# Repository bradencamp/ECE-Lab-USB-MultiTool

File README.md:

# USB-ECE-Lab-Multitool
In recent years students have been required to purchase USB Laboratory Instruments such as the Analog Discovery 2 (AD2) from Digilent Inc or the Advanced Active Learning Module (ADALM 2000) from Analog Devices. These devices allow the students to complete Laboratory exercises at home and to experiment on their own time without the need to rely on open lab hours. The COVID pandemic created a high demand for such devices, as throughout the U.S. lab classes have been converted to at-home labs. This high demand in concert with the chip crises has propelled the price for these devices to currently $199 and $249 (academic price for the AD2 and AD3, respectively) and $237 (ADALM2000).

This USB Multi-function Laboratory Instrument will be inexpensive and therefore less capable than the AD2 or ADALM 2000 while still fulfilling the requirements for most laboratory exercises in the undergraduate ECE curriculum. This new device should use a microcontroller with analog front ends for the Oscilloscope and Wave Form Generator functionality. It should function as a 2-channel Oscilloscope and Arbitrary Waveform Generator (AWG) with a Bandwidth of up to 2 MHz and a sample rate of 5 Msps, a 16-channel logic analyzer, and be controllable via USB from a PC (Windows, Mac, and Linux) as well as offering live waveform viewing on a PC. The total part cost should not exceed $50. A similar project was once offered by the Opencope MZ (https://digilent.com/reference/test-and-measurement/openscope-mz/start) which has been discontinued.

Previous senior design projects have built a one-channel prototype for the oscilloscope and a two channel AWG. However, the oscilloscope did not fully meet the requirements. The arbitrary waveform generator function is complete. The logic analyzer is now a separate project and currently being designed. The goal of this project is to learn from the oscilloscope prototype and create one that meets the requirements and integrate the arbitrary waveform generator and the logic analyzer, all with an intuitive and easy to use graphical user interface on the PC using PyQtGraph. This project requires analog circuit design of amplifiers, filters, etc., while being cost-conscious. The fewer different parts are needed and the fewer parts are needed overall, the more likely you'll meet the $50 target. It also requires programming of an STM-32 microcontroller in C, GUI design and programming in Python.

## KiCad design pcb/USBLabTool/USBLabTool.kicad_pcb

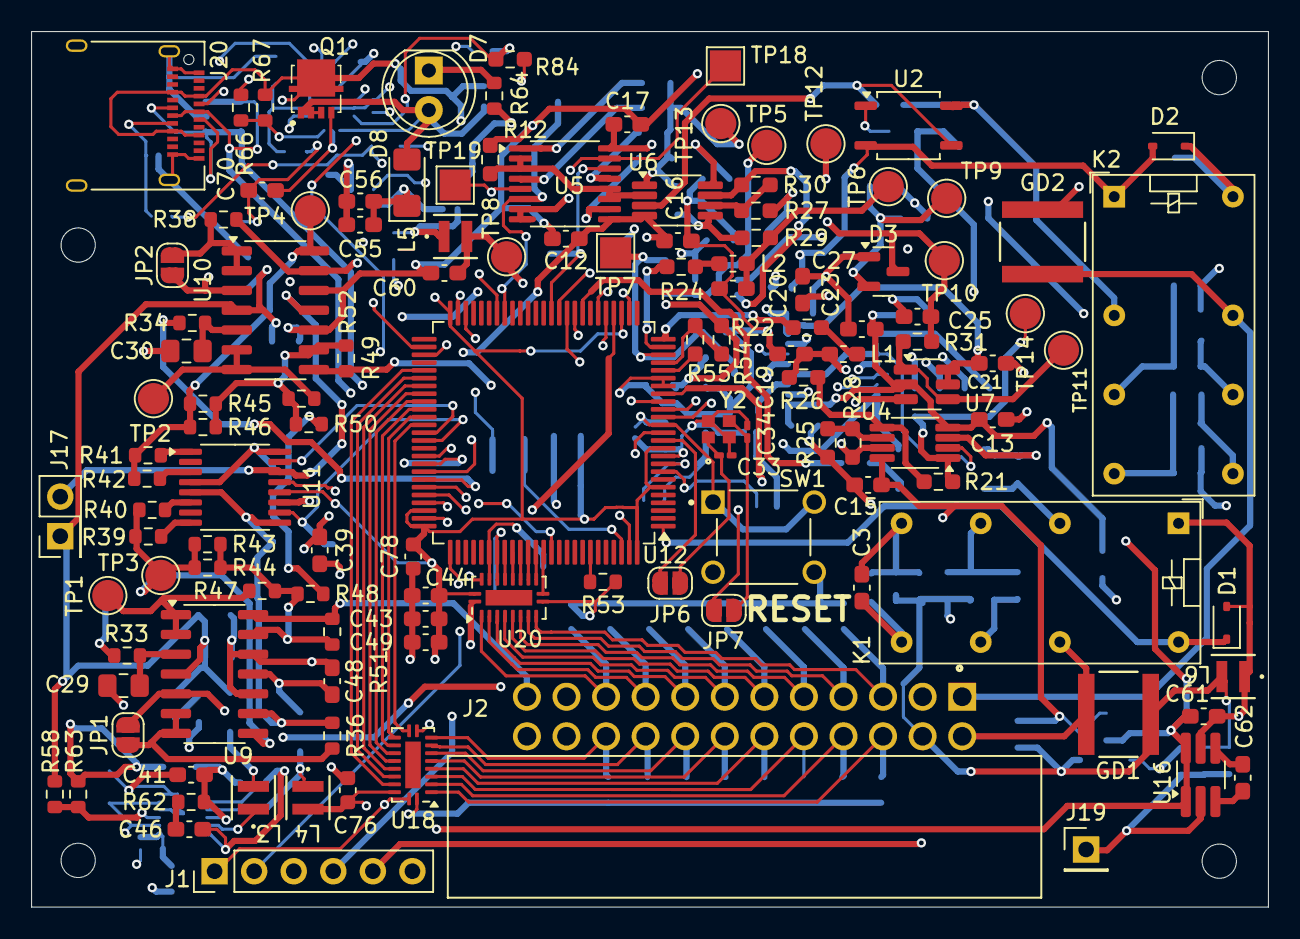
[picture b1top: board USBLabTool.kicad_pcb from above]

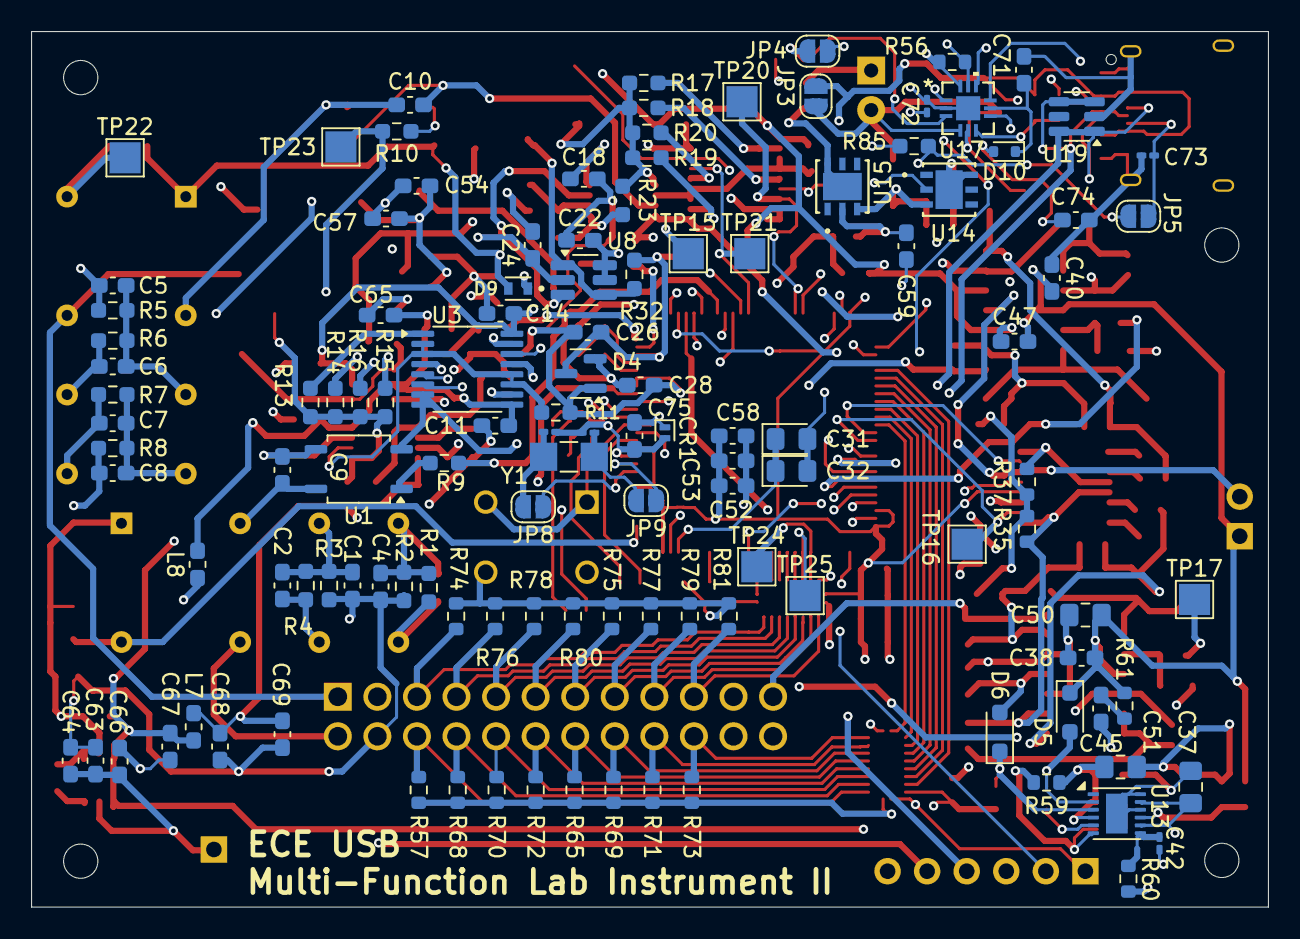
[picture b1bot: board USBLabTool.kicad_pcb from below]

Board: 4 copper layers, 79.4 x 56.2 mm, 250 parts (121 on the bottom side), 165 nets.

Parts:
C1, C5: 200p; C_0603_1608Metric_Pad1.08x0.95mm_HandSolder
C2, C4, C6, C8: 820p; C_0603_1608Metric_Pad1.08x0.95mm_HandSolder
C3, C7: 68p; C_0603_1608Metric_Pad1.08x0.95mm_HandSolder
C9, C10: 47n; C_0603_1608Metric_Pad1.08x0.95mm_HandSolder
C11, C12, C13, C14, C15, C16, C17, C18, C21, C22, C23, C24, C27, C28, C38, C39, C40, C41, C43, C44, C47, C48, C49, C52, C53, C54, C63, C64, C65, C67, C68, C69, C71, C75: 100n; C_0603_1608Metric_Pad1.08x0.95mm_HandSolder
C19, C20, C62: 1u; C_0603_1608Metric_Pad1.08x0.95mm_HandSolder
C25, C26: 160p; C_0603_1608Metric_Pad1.08x0.95mm_HandSolder
C29, C30, C37, C50, C51: 10u; C_0805_2012Metric_Pad1.18x1.45mm_HandSolder
C31, C32: 2.2u; D_0805_2012Metric_Pad1.15x1.40mm_HandSolder
C33, C34: 5.6p; C_0201_0603Metric_Pad0.64x0.40mm_HandSolder
C35, C36: 3.3p; C_0201_0603Metric_Pad0.64x0.40mm_HandSolder
C42: 100n; C_0201_0603Metric_Pad0.64x0.40mm_HandSolder
C45, C46: 120p; C_0603_1608Metric_Pad1.08x0.95mm_HandSolder
C55, C56, C58: 4.7uF; C_0603_1608Metric_Pad1.08x0.95mm_HandSolder
C57, C61, C66: 10u; C_0603_1608Metric_Pad1.08x0.95mm_HandSolder
C59, C60: 100nF; C_0603_1608Metric_Pad1.08x0.95mm_HandSolder
C70: DNF; C_0603_1608Metric_Pad1.08x0.95mm_HandSolder
C72, C73: 330p; C_0201_0603Metric_Pad0.64x0.40mm_HandSolder
C74: 2.2u; C_0603_1608Metric_Pad1.08x0.95mm_HandSolder
C76, C78: 100nF; C_0603_1608Metric
CR1: ESDALC6V1-1M2; D_SOD-882
D1, D2: 1N4148WS; D_SOD-323
D3, D4: BAV99; SOT-23
D5, D6: NSR0530; D_SOD-323_HandSoldering
D7: LED; LED_D5.0mm
D8: D_Schottky; D_1206_3216Metric_Pad1.42x1.75mm_HandSolder
D9: ESDA25P35-1U1M; TVS_ESDA25P35-1U1M
D10: BAT54KFILM; D_SOD-523
GD1, GD2: GDT_SH90; GDT_SH_LTF
H1, H2, H3, H4: MountingHole; MountingHole_2.2mm_M2
J1: Conn_01x06_Pin; PinHeader_1x06_P2.54mm_Vertical
J2: Conn_02x12_Odd_Even; OST_302-R241
J17: 2x01; PinHeader_2x01_P2.54mm_Vertical
J19: T_N5V; PinHeader_1x01_P2.54mm_Vertical
J20: USB_C_Receptacle; USB_C_Receptacle_Amphenol_12401610E4-2A
JP1, JP2, JP3, JP4, JP5, JP6, JP7, JP8, JP9: SJ; SolderJumper-2_P1.3mm_Open_RoundedPad1.0x1.5mm
K1, K2: G5V-2; Relay_DPDT_Omron_G5V-2
L1, L2: 10uH; L_0603_1608Metric_Pad1.05x0.95mm_HandSolder
L3, L4, L5, L6: 4.7uH; IND_TAIYO_NRH2410_TAY
L7, L8: 4.7uH; L_0603_1608Metric_Pad1.05x0.95mm_HandSolder
Q1: STL11N3LLH6; STL20N6F7
R1, R3, R5, R7: 820K; R_0603_1608Metric_Pad0.98x0.95mm_HandSolder
R2, R8: 68K; R_0603_1608Metric_Pad0.98x0.95mm_HandSolder
R4, R6: 200k; R_0603_1608Metric_Pad0.98x0.95mm_HandSolder
R9, R10: 240; R_0603_1608Metric_Pad0.98x0.95mm_HandSolder
R11, R12, R21, R23, R28, R30: 1K; R_0603_1608Metric_Pad0.98x0.95mm_HandSolder
R13, R17, R22, R24: 6.2; R_0603_1608Metric_Pad0.98x0.95mm_HandSolder
R14, R18: 1.5K; R_0603_1608Metric_Pad0.98x0.95mm_HandSolder
R15, R19: 3.9K; R_0603_1608Metric_Pad0.98x0.95mm_HandSolder
R16, R20: 9.1K; R_0603_1608Metric_Pad0.98x0.95mm_HandSolder
R25, R26, R27, R29: 2K; R_0603_1608Metric_Pad0.98x0.95mm_HandSolder
R31, R32: 100; R_0603_1608Metric_Pad0.98x0.95mm_HandSolder
R33, R34, R35, R37, R40, R42, R43, R44, R45, R46, R48, R50, R51, R52, R53, R56, R60, R63, R67: 10K; R_0603_1608Metric
R36, R38, R47, R49: 3K3; R_0603_1608Metric
R39, R41, R61, R62, R64: 1K; R_0603_1608Metric
R54, R55: 0; R_0603_1608Metric_Pad0.98x0.95mm_HandSolder
R57, R65, R68, R69, R70, R71, R72, R73, R74, R75, R76, R77, R78, R79, R80, R81: 1M; R_0603_1608Metric
R58: 110k; R_0603_1608Metric
R59: 100k; R_0603_1608Metric
R66: 2.4K; R_0603_1608Metric
R84, R85: 5.1k; R_0603_1608Metric_Pad0.98x0.95mm_HandSolder
SW1: TS02-66-73-BK-100-SCR-D; SW_TS02-66-73-BK-100-SCR-D
TP1, TP2, TP3, TP4: TestPoint; TestPoint_Pad_D2.0mm
TP5: T_buf_0; TestPoint_Pad_D2.0mm
TP6: T_pwm_0; TestPoint_Pad_D2.0mm
TP7: T_adc_0; TestPoint_Pad_2.0x2.0mm
TP8, TP9: +3.3VA; TestPoint_Pad_D2.0mm
TP10: T_adc_1; TestPoint_Pad_D2.0mm
TP11: T_buf_1; TestPoint_Pad_D2.0mm
TP12: T_pwm_1; TestPoint_Pad_D2.0mm
TP13: T_amp_0; TestPoint_Pad_D2.0mm
TP14: T_amp_1; TestPoint_Pad_D2.0mm
TP15, TP16, TP17, TP18, TP19, TP20, TP21, TP22, TP23, TP24, TP25: TestPoint; TestPoint_Pad_2.0x2.0mm
U1, U2: AQY284SX; SOP-4_3.8x4.1mm_P2.54mm
U3, U5: CD74HC4316; TSSOP-16_4.4x5mm_P0.65mm
U4, U6: LMP7718; VSSOP-8_3x3mm_P0.65mm
U7, U8: OPA863; SOT-23-6_Handsoldering
U9, U10: MC33274ADR2G; SOIC-14_3.9x8.7mm_P1.27mm
U11: DG403; TSSOP-16_4.4x5mm_P0.65mm
U12: STM32H563VITx; LQFP-100_14x14mm_P0.5mm
U13: R1283K002A; ST_UFDFPN-12-1EP_3x3mm_P0.5mm_EP1.4x2.55mm
U14, U15: ST1L05APU33R; DFN_5APU33R_STM
U16: LTC1983ES6-5TRMPBF; TSOT-23-6_HandSoldering
U17: TCPP01-M12; QFN12_TCPP01-M12_STM
U18, U20: 74HC245; DHVQFN-20-1EP_2.5x4.5mm_P0.5mm_EP1x3mm
U19: USBLC6-2SC6; SOT-23-6
Y1: 32.768kHz; Crystal_SMD_MicroCrystal_CC7V-T1A-2Pin_3.2x1.5mm_HandSolder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
Y2: NX2016SA-25M-EXS00A-CS08742; NX2016SA_NDK

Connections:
+3.3V: C43.1, C44.1, C49.1, C52.1, C53.1, C58.2, C76.1, C78.1, J1.1, R56.1, U11.12 (VL), U12.6 (VBAT), U12.11 (VDD), U12.28 (VDD), U12.50 (VDD), U12.73 (VDDUSB), U12.75 (VDD), U12.100 (VDD), U14.2 (VO), U17.12 (VCC), U18.20 (VCC), U20.20 (VCC)
+3.3VA: C27.1, C28.1, C54.1, C57.1, C60.2, D3.2 (A), D4.2 (A), L5.2, R54.1, TP8.1, TP9.1
+5V: C37.1, C61.1, C67.1, D7.2 (A), D8.2 (A), JP3.1 (A), L3.1, L7.1, Q1.1 (S_1), Q1.2 (S_2), Q1.3 (S_3), U13.5 (CE), U13.8 (Vcc), U13.11 (PVcc), U16.1 (VCC), U16.6 (~SHDN), U17.4 (SOURCE)
+5VCLEAN: C14.1, C15.1, C17.1, C18.1, C21.2, C22.2, C68.1, C69.1, L7.2, U3.16 (V_CC), U4.8 (V+), U5.16 (V_CC), U6.8 (V+), U7.5 (~DISABLE), U7.6 (V+), U8.5 (~DISABLE), U8.6 (V+)
+12VA: C38.1, C40.2, C47.1, C50.1, D5.1 (K), J17.1, R58.1, R61.1, U9.4 (V+), U10.4 (V+), U11.11 (V+)
-5V: C63.1, C64.1, C66.1, J19.1, L8.1, U16.2 (VOUT)
-5VCLEAN: C11.1, C12.1, C13.1, C16.1, C23.1, C24.1, C65.1, L8.2, R35.1, R37.1, R48.2, R50.2, U3.9 (V_EE), U4.4 (V-), U5.9 (V_EE), U6.4 (V-), U7.2 (V-), U8.2 (V-)
-12VA: C39.2, C41.2, C48.2, C51.2, D6.2 (A), J17.2, R59.1, R62.1, U9.11 (V-), U10.11 (V-), U11.14 (V-), U13.4 (Voutn)
/AWG_FrontEnd/C0_FB: R35.2, R36.2, U9.9 (-), U11.5 (S4), U11.9 (S2)
/AWG_FrontEnd/C0_OUT_G: R39.2, R40.2, R43.2, R44.1, TP3.1, U9.8
/AWG_FrontEnd/C0_V_OFF: R47.1, TP1.1, U9.1, U9.2 (-)
/AWG_FrontEnd/C1_FB: R37.2, R38.2, U10.13 (-), U11.4 (S3), U11.16 (S1)
/AWG_FrontEnd/C1_OUT_G: R41.2, R42.1, R45.1, R46.1, TP4.1, U10.14
/AWG_FrontEnd/C1_V_OFF: R49.1, TP2.1, U10.6 (-), U10.7
ADC1_INP0: C26.1, D4.3 (K), R32.2, TP7.1, U12.23 (PA0)
ADC2_INP3: C25.1, D3.3 (K), R31.2, TP10.1, U12.31 (PA6)
C0_IN: JP1.1 (A), U9.5 (+), U12.29 (PA4)
C1_IN: JP2.1 (A), U10.3 (+), U12.30 (PA5)
CH0_ACDC: R10.2, TP23.1, U12.18 (PC3)
CH0_amp_1: TP18.1, U5.15 (1S), U12.36 (PB1)
CH0_amp_2.5: TP19.1, U5.5 (2S), U12.44 (PE13)
CH0_amp_5: TP20.1, U5.6 (3S), U12.43 (PE12)
CH0_amp_10: TP21.1, U5.14 (4S), U12.37 (PB2)
CH0_attenuate: D2.1 (K), K2.16, TP22.1, U12.17 (PC2)
CH1_ACDC: R9.2, U12.33 (PC4)
CH1_amp_1: U3.15 (1S), U12.34 (PC5)
CH1_amp_2.5: U3.5 (2S), U12.16 (PC1)
CH1_amp_5: U3.6 (3S), U12.15 (PC0)
CH1_amp_10: U3.14 (4S), U12.35 (PB0)
CH1_attenuate: D1.1 (K), K1.16, U12.1 (PE2)
DAC1_OUT1: J2.23, R51.2, U9.14
DAC1_OUT2: J2.24, R52.2, U10.8
DEBUG_JTCK_SWCLK: J1.2, U12.76 (PA14(JTCK)
DEBUG_JTD-SW0: J1.6, U12.89 (PB3(JTDO)
DEBUG_JTMS-SWDI0: J1.4, U12.72 (PA13(JTMS)
GAIN_C0: TP16.1, U11.10 (IN2), U12.64 (PC7)
GAIN_C1: U11.15 (IN1), U12.63 (PC6)
GND: C29.2, C30.2, C33.2, C34.1, C35.1, C36.1, C37.2, C40.1, C41.1, C42.2, C43.2, C44.2, C49.2, C52.2, C53.2, C55.2, C56.2, C58.1, C59.1, C61.2, C66.2, C67.2, C71.1, C72.1, C73.1, C74.1, C75.2, C76.2, C78.2, CR1.2 (A), D1.2 (A), D2.2 (A), D9.A, J1.3, J2.3, J2.21, J20.A1 (GND), J20.A12 (GND), J20.B1 (GND), J20.B12 (GND), J20.S1 (SHIELD), K1.1, K2.1, L4.2, L6.1, R53.1, R57.2, R64.2, R65.1, R66.2, R68.2, R69.1, R70.2, R71.1, R72.2, R73.1, R74.1, R75.2, R76.1, R77.2, R78.1, R79.2, R80.1, R81.2, SW1.3 (K), SW1.4 (A), U1.2, U2.2, U3.7 (E), U3.8 (GND), U5.7 (E), U5.8 (GND), U11.13 (GND), U12.10 (VSS), U12.27 (VSS), U12.49 (VSS), U12.74 (VSS), U12.99 (VSS), U13.10 (GND), U13.12 (PGND), U13.13 (GND), U14.6 (GND), U14.7 (GND), U15.6 (GND), U15.7 (GND), U16.5 (GND), U17.2 (GND), U17.13 (GND), U18.1 (A->B), U18.10 (GND), U18.19 (CE), U19.2 (GND), U20.1 (A->B), U20.10 (GND), U20.19 (CE), Y2.2, Y2.4
GNDA: C1.1, C4.2, C5.1, C8.2, C11.2, C12.2, C13.2, C14.2, C15.2, C16.2, C17.2, C18.2, C19.2, C20.2, C21.1, C22.1, C23.2, C24.2, C25.2, C26.2, C27.2, C28.2, C38.2, C39.1, C47.2, C48.1, C50.2, C51.1, C54.2, C57.2, C60.1, C63.2, C64.2, C65.2, C68.2, C69.2, D3.1 (K), D4.1 (K), GD1.1, GD2.1, J2.4, J2.22, L6.2, R2.1, R3.1, R5.1, R8.1, R11.1, R12.1, R25.2, R27.2, R63.1, U9.10 (+), U9.12 (+), U10.10 (+), U10.12 (+), U12.19 (VSSA), U12.20 (VREF-)
LOGIC_IN0: TP24.1, U12.81 (PD0), U20.18 (B0)
LOGIC_IN1: TP25.1, U12.82 (PD1), U20.17 (B1)
LOGIC_IN2: U12.83 (PD2), U20.16 (B2)
LOGIC_IN3: U12.84 (PD3), U20.15 (B3)
LOGIC_IN4: U12.85 (PD4), U20.14 (B4)
LOGIC_IN5: U12.86 (PD5), U20.13 (B5)
LOGIC_IN6: U12.87 (PD6), U20.12 (B6)
LOGIC_IN7: U12.88 (PD7), U20.11 (B7)
LOGIC_IN8: U12.62 (PD15), U18.11 (B7)
LOGIC_IN9: U12.61 (PD14), U18.12 (B6)
LOGIC_IN10: U12.60 (PD13), U18.13 (B5)
LOGIC_IN11: U12.59 (PD12), U18.14 (B4)
LOGIC_IN12: U12.58 (PD11), U18.15 (B3)
LOGIC_IN13: U12.57 (PD10), U18.16 (B2)
LOGIC_IN14: U12.56 (PD9), U18.17 (B1)
LOGIC_IN15: U12.55 (PD8), U18.18 (B0)
LOGIC_INP0: J2.19, R81.1, U20.2 (A0)
LOGIC_INP1: J2.17, R79.1, U20.3 (A1)
LOGIC_INP2: J2.15, R77.1, U20.4 (A2)
LOGIC_INP3: J2.13, R75.1, U20.5 (A3)
LOGIC_INP4: J2.11, R80.2, U20.6 (A4)
LOGIC_INP5: J2.9, R78.2, U20.7 (A5)
LOGIC_INP6: J2.7, R76.2, U20.8 (A6)
LOGIC_INP7: J2.5, R74.2, U20.9 (A7)
LOGIC_INP8: J2.20, R73.2, U18.9 (A7)
LOGIC_INP9: J2.18, R71.2, U18.8 (A6)
LOGIC_INP10: J2.16, R69.2, U18.7 (A5)
LOGIC_INP11: J2.14, R65.2, U18.6 (A4)
LOGIC_INP12: J2.12, R72.1, U18.5 (A3)
LOGIC_INP13: J2.10, R70.1, U18.4 (A2)
LOGIC_INP14: J2.8, R68.1, U18.3 (A1)
LOGIC_INP15: J2.6, R57.1, U18.2 (A0)
NRST: C75.1, CR1.1 (K), J1.5, SW1.1, SW1.2, U12.14 (NRST)
unnamed: C1.2, C2.1, K1.6, R3.2, R4.1
unnamed: C2.2, K1.11, R4.2
unnamed: C3.1, K1.9, R1.2
unnamed: C3.2, C4.1, K1.8, R1.1, R2.2
unnamed: C5.2, C6.1, K2.6, R5.2, R6.1
unnamed: C6.2, K2.11, R6.2
unnamed: C7.1, K2.9, R7.2
unnamed: C7.2, C8.1, K2.8, R7.1, R8.2
unnamed: C9.1, K1.4, U1.4
unnamed: C10.1, K2.4, U2.4
unnamed: C19.1, L1.2, R26.1, TP12.1
unnamed: C20.1, L2.2, R29.1, TP6.1
unnamed: C31.1, C32.1, U12.98 (VCAP)
unnamed: C31.2, C32.2, U12.48 (VCAP)
unnamed: C45.1, R61.2
unnamed: C46.1, R62.2
unnamed: D5.2 (A), L3.2, U13.2 (Lx1)
unnamed: D6.1 (K), L4.1, U13.3 (Lx2)
unnamed: D7.1 (K), R64.1
unnamed: C55.1, C56.1, D8.1 (K), U14.3 (VI), U15.3 (VI)
unnamed: C70.1, C74.2, D9.C, D10.2 (A), J20.A4 (VBUS), J20.A9 (VBUS), J20.B4 (VBUS), J20.B9 (VBUS), JP3.2 (B), Q1.5 (D), R67.1
unnamed: C71.2, D10.1 (K), U17.8 (IN_GD)
unnamed: C72.2, J20.A5 (CC1), JP4.2 (B), U17.7 (CC1c)
unnamed: C73.2, J20.B5 (CC2), JP5.2 (B), U17.9 (CC2c)
unnamed: JP1.2 (B), R36.1, U9.6 (-), U9.7
unnamed: JP2.2 (B), R38.1, U10.1, U10.2 (-)
unnamed: C33.1, JP6.2 (B), Y2.1
unnamed: C34.2, JP7.1 (A), Y2.3
unnamed: C35.2, JP8.2 (B), Y1.2
unnamed: C36.2, JP9.2 (B), Y1.1
unnamed: L1.1, R22.2
unnamed: L2.1, R24.2
unnamed: C70.2, Q1.4 (G), U17.5 (GATE)
unnamed: R9.1, U1.1
unnamed: R10.1, U2.1
unnamed: R11.2, U3.2 (1Y), U3.3 (2Y), U3.11 (3Y), U3.12 (4Y), U4.2 (-IN_A)
unnamed: R13.1, U3.1 (1Z)
unnamed: R14.1, U3.4 (2Z)
unnamed: R15.1, U3.10 (3Z)
unnamed: R16.1, U3.13 (4Z)
unnamed: C9.2, U1.3, U4.3 (+IN_A)
unnamed: R21.2, R26.2, U4.5 (+IN_B)
unnamed: R25.1, R28.1, U4.6 (-IN_B)
unnamed: R13.2, R14.2, R15.2, R16.2, R21.1, TP14.1, U4.1 (OUT_A)
unnamed: R28.2, U4.7 (OUT_B), U7.3 (+)
unnamed: R12.2, U5.2 (1Y), U5.3 (2Y), U5.11 (3Y), U5.12 (4Y), U6.2 (-IN_A)
unnamed: R17.1, U5.1 (1Z)
unnamed: R18.1, U5.4 (2Z)
unnamed: R19.1, U5.10 (3Z)
unnamed: R20.1, U5.13 (4Z)
unnamed: C10.2, U2.3, U6.3 (+IN_A)
unnamed: R23.2, R29.2, U6.5 (+IN_B)
unnamed: R27.1, R30.1, U6.6 (-IN_B)
unnamed: R17.2, R18.2, R19.2, R20.2, R23.1, TP13.1, U6.1 (OUT_A)
unnamed: R30.2, U6.7 (OUT_B), U8.3 (+)
unnamed: R31.1, TP11.1, U7.1, U7.4 (-)
unnamed: R32.1, TP5.1, U8.1, U8.4 (-)
unnamed: C29.1, R33.2, U9.3 (+)
unnamed: R43.1, R44.2, R47.2, R48.1, R51.1, U9.13 (-)
unnamed: C30.1, R34.2, U10.5 (+)
unnamed: R45.2, R46.2, R49.2, R50.1, R52.1, U10.9 (-)
unnamed: R41.1, U11.1 (D1)
unnamed: R42.2, U11.3 (D3)
unnamed: R39.1, U11.8 (D2)
unnamed: R40.1, U11.6 (D4)
unnamed: R53.2, U12.94 (BOOT0)
unnamed: R84.1, U12.52 (PB13)
unnamed: R85.1, U12.53 (PB14)
unnamed: R54.2, R55.2, U12.22 (VDDA)
unnamed: C45.2, R58.2, R63.2, U13.9 (Vfb1)
unnamed: C46.2, R59.2, R60.1, U13.6 (Vfb2)
unnamed: C42.1, R60.2, U13.7 (Vref)
unnamed: C59.2, L5.1, U15.2 (VO)
unnamed: C62.1, U16.3 (C+)
unnamed: C62.2, U16.4 (C-)
unnamed: R66.1, R67.2, U17.6 (VBUS_CTRL)
P_CH0_IN: GD2.2, J2.1, K2.13
P_CH1_IN: GD1.2, J2.2, K1.13
RCC_OSC32_IN: JP8.1 (A), U12.8 (PC14)
RCC_OSC32_OUT: JP9.1 (A), U12.9 (PC15)
RCC_OSC_IN: JP6.1 (A), U12.12 (PH0)
RCC_OSC_OUT: JP7.2 (B), U12.13 (PH1)
TIM1_CH1: R33.1, TP17.1, U12.67 (PA8)
TIM1_CH2: R34.1, U12.69 (PA10)
TIM2_CH2: R24.1, TP15.1, U12.24 (PA1)
TIM2_CH3: R22.1, U12.25 (PA2)
UCPD_CC1: JP4.1 (A), R84.2, U17.3 (CC1)
UCPD_CC2: JP5.1 (A), R85.2, U17.1 (CC2)
UCPD_FLT: R56.2, U12.66 (PC9), U17.11 (FLT/)
USB_D+: J20.A6 (D+), J20.B6 (D+), U12.71 (PA12), U19.3 (I/O2), U19.4 (I/O2)
USB_D-: J20.A7 (D-), J20.B7 (D-), U12.70 (PA11), U19.1 (I/O1), U19.6 (I/O1)
USCPD_DBn: U12.68 (PA9), U17.10 (DB/)
VREFP: R55.1, U12.21 (VREF+)

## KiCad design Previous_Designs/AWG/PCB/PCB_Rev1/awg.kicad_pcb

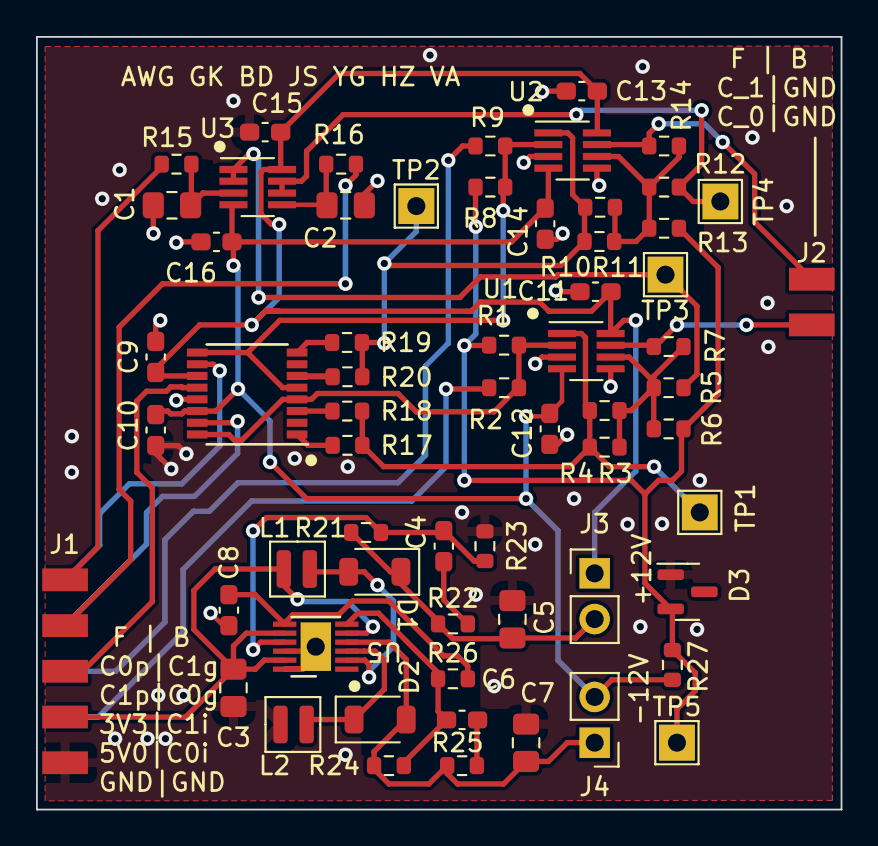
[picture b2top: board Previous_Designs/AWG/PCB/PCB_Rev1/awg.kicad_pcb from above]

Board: 2 copper layers, 44.7 x 42.9 mm, 62 parts (0 on the bottom side), 37 nets.

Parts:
C1, C2, C3, C5, C7: 10u; C_0805_2012Metric_Pad1.18x1.45mm_HandSolder
C4, C6: 120p; C_0603_1608Metric_Pad1.08x0.95mm_HandSolder
C8, C9, C10, C11, C12, C13, C14, C15, C16: 100n; C_0603_1608Metric_Pad1.08x0.95mm_HandSolder
D1, D2: S14
D3: LM4040-5; SOT-23
J1: 02x05; 2x05
J2: 02x02; 2x02
J3, J4: 01x02; PinHeader_1x02_P2.54mm_Vertical
L1, L2: 4.7u; NRH2410
R1, R3, R4, R6, R7, R8, R10, R11, R13, R14, R18, R20, R23, R26: 10K; R_0603_1608Metric
R2, R5, R9, R12: 3K3; R_0603_1608Metric
R15, R16, R17, R19, R22, R25, R27: 1K; R_0603_1608Metric
R21: 110k; R_0603_1608Metric
R24: 100k; R_0603_1608Metric
TP1, TP2, TP3, TP4, TP5: TestPoint; TestPoint_THTPad_2.0x2.0mm_Drill1.0mm
U1, U2, U3: LM2904; SOT-23-8_Handsoldering
U4: DG403; TSSOP-16-1EP_4.4x5mm_P0.65mm
U5: r1283; DFN-12

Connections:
+3.3V: J1.3, U4.12 (VL)
+5V: C3.1, J1.4, L1.1, U5.5 (CE), U5.8 (Vcc), U5.11 (PVcc)
+12V: C9.2, C11.1, C13.1, C15.1, J3.1, U1.8 (V+), U2.8 (V+), U3.8 (V+), U4.11 (V+)
-5V: D3.2 (A), R1.1, R6.2, R8.1, R13.2, R27.1, TP5.1
-12V: C10.2, C12.2, C14.2, C16.2, J4.2, R27.2, U1.4 (V-), U2.4 (V-), U3.4 (V-), U4.14 (V-)
/C0_FB: R1.2, R2.2, U1.2 (-), U4.4 (S3), U4.16 (S1)
/C0_IN: J1.9, R2.1
/C0_OUT_G: R3.2, R4.1, R17.2, R18.1, TP1.1, U1.1
/C0_OUT_GO: J2.2, R7.2, U1.7
/C0_PWM_OFF: J1.1, R15.1
/C0_S_GAIN: J1.7, U4.15 (IN1)
/C0_V_OFF: R5.1, TP3.1, U3.1, U3.2 (-)
/C1_FB: R8.2, R9.2, U2.2 (-), U4.5 (S4), U4.9 (S2)
/C1_IN: J1.8, R9.1
/C1_OUT_G: R10.1, R11.1, R19.2, R20.2, TP2.1, U2.1
/C1_OUT_GO: J2.1, R14.2, U2.7
/C1_PWM_OFF: J1.2, R16.1
/C1_S_GAIN: J1.6, U4.10 (IN2)
/C1_V_OFF: R12.1, TP4.1, U3.6 (-), U3.7
GND: C1.2, C2.2, C3.2, C5.2, C7.1, C8.2, C9.1, C10.1, C11.2, C12.1, C13.2, C14.1, C15.2, C16.1, D3.1 (K), J1.5, J1.10, J2.3, J2.4, L2.2, R23.1, U1.3 (+), U1.5 (+), U2.3 (+), U2.5 (+), U4.13 (GND), U5.10 (GND), U5.12 (PGND), U5.13 (GND)
unnamed: C4.1, R22.2
unnamed: C6.1, R25.2
unnamed: D1.2 (A), L1.2, U5.2 (Lx1)
unnamed: C5.1, D1.1 (K), J3.2, R21.1, R22.1
unnamed: C7.2, D2.2 (A), J4.1, R24.1, R25.1, U5.4 (Voutn)
unnamed: D2.1 (K), L2.1, U5.3 (Lx2)
unnamed: R3.1, R4.2, R5.2, R6.1, R7.1, U1.6 (-)
unnamed: R10.2, R11.2, R12.2, R13.1, R14.1, U2.6 (-)
unnamed: C1.1, R15.2, U3.3 (+)
unnamed: C2.1, R16.2, U3.5 (+)
unnamed: R17.1, U4.1 (D1)
unnamed: R19.1, U4.8 (D2)
unnamed: R18.2, U4.3 (D3)
unnamed: R20.1, U4.6 (D4)
unnamed: C4.2, R21.2, R23.2, U5.9 (Vfb1)
unnamed: C6.2, R24.2, R26.1, U5.6 (Vfb2)
unnamed: C8.1, R26.2, U5.7 (Vref)

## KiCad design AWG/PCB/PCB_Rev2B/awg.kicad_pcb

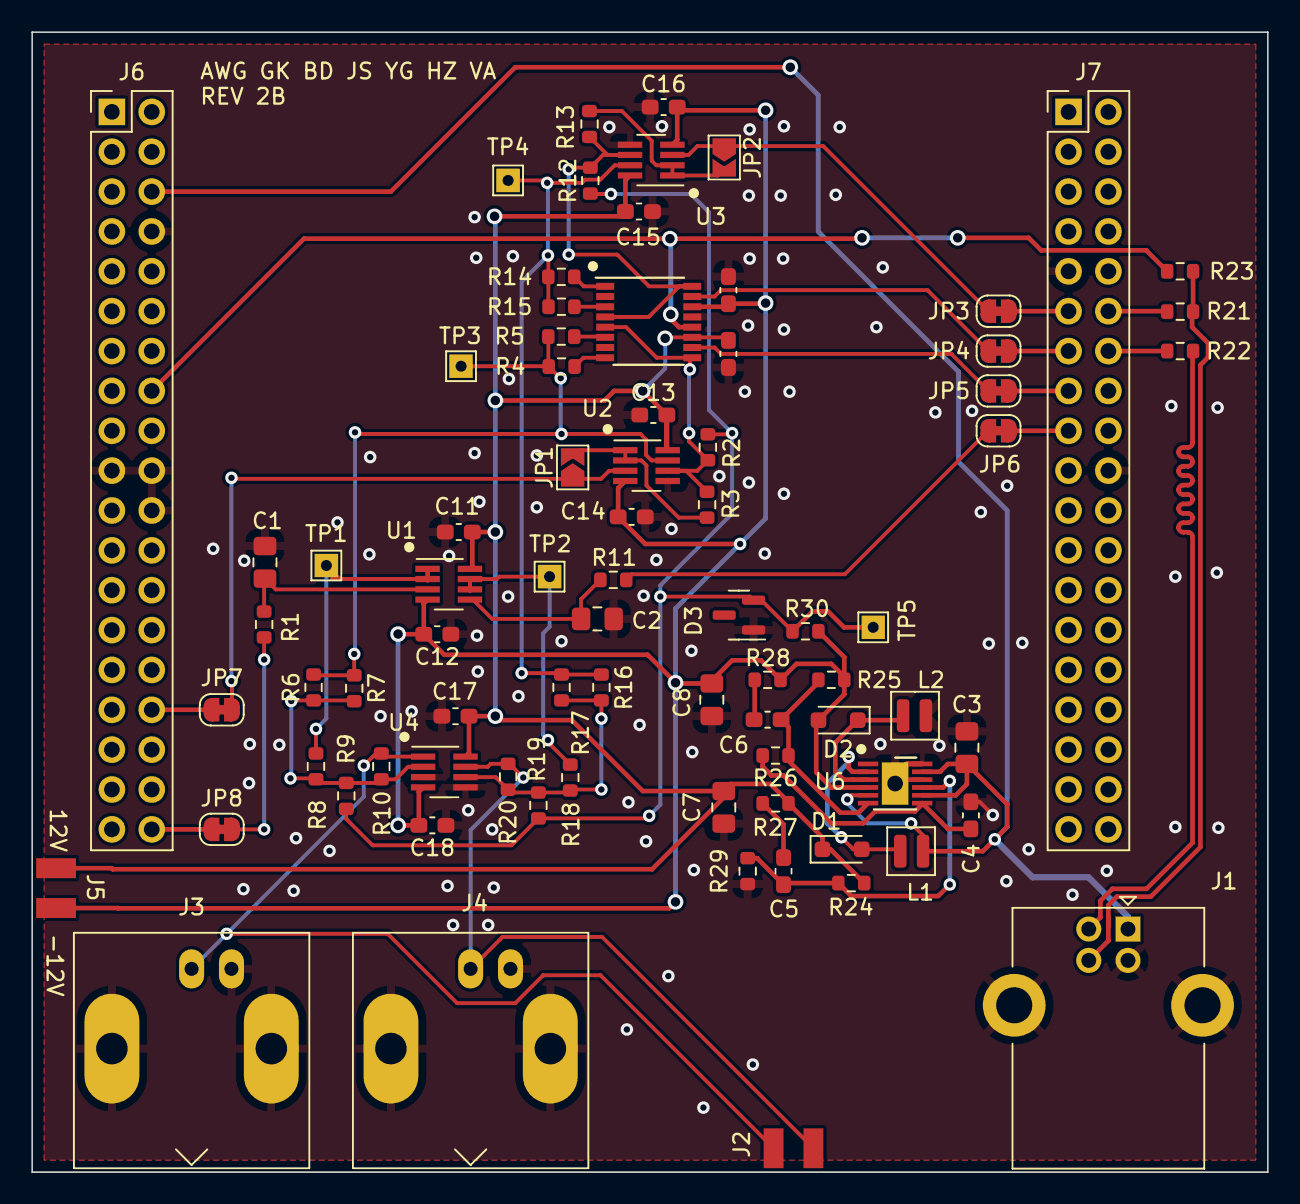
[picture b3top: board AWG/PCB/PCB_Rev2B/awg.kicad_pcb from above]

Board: 2 copper layers, 78.7 x 72.6 mm, 79 parts (0 on the bottom side), 47 nets.

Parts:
C1, C2, C3, C7, C8: 10u; C_0805_2012Metric_Pad1.18x1.45mm_HandSolder
C4, C9, C10, C11, C12, C13, C14, C15, C16, C17, C18: 100n; C_0603_1608Metric_Pad1.08x0.95mm_HandSolder
C5, C6: 120p; C_0603_1608Metric_Pad1.08x0.95mm_HandSolder
D1, D2: S14; D_SOD-323_HandSoldering
D3: LM4040-5; SOT-23
J1: USB_B; USB_B_Lumberg_2411_02_Horizontal
J2: 02x02; 2x02
J3, J4: BNC; BNC_Amphenol_B6252HB-NPP3G-50_Horizontal
J5: 2x01; 1x02
J6: nuc303_LEFT; PinHeader_2x19_P2.54mm_Vertical
J7: nuc303_RIGHT; PinHeader_2x19_P2.54mm_Vertical
JP1, JP2: SJ; SolderJumper-2_P1.3mm_Open_TrianglePad1.0x1.5mm
JP3, JP4, JP5, JP6, JP7, JP8: JP; SolderJumper-2_P1.3mm_Bridged_RoundedPad1.0x1.5mm
L1, L2: 4.7u; NRH2410
R1, R2, R5, R6, R7, R9, R10, R11, R12, R15, R16, R17, R19, R20, R26, R29: 10K; R_0603_1608Metric
R3, R8, R13, R18: 3K3; R_0603_1608Metric
R4, R14, R27, R28, R30: 1K; R_0603_1608Metric
R21, R22: 22; R_0603_1608Metric
R23: 1K5; R_0603_1608Metric
R24: 110k; R_0603_1608Metric
R25: 100k; R_0603_1608Metric
TP1, TP2, TP3, TP4, TP5: TestPoint; TestPoint_THTPad_1.5x1.5mm_Drill0.7mm
U1, U2, U3, U4: LM2904; SOT-23-8_Handsoldering
U5: DG403; TSSOP-16-1EP_4.4x5mm_P0.65mm
U6: r1283; DFN-12

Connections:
+3.3V: J6.16 (3V3), R23.2, U5.12 (VL)
+5V: C3.1, J1.1 (VBUS), J6.6 (E5V), L1.1, U6.5 (CE), U6.8 (Vcc), U6.11 (PVcc)
+12V: C7.1, C9.2, C11.1, C13.1, C15.1, C17.1, D1.1 (K), J5.1, R24.1, R27.1, U1.8 (V+), U2.8 (V+), U3.8 (V+), U4.8 (V+), U5.11 (V+)
-5V: D3.2 (A), R2.1, R9.2, R12.1, R19.2, R30.1, TP5.1
-12V: C8.2, C10.2, C12.2, C14.2, C16.2, C18.2, D2.2 (A), J5.2, R25.1, R28.1, R30.2, U1.4 (V-), U2.4 (V-), U3.4 (V-), U4.4 (V-), U5.14 (V-), U6.4 (Voutn)
/C0_FB: R2.2, R3.2, U2.6 (-), U5.5 (S4), U5.9 (S2)
/C0_IN: JP1.1 (A), JP7.2 (B), U2.3 (+)
/C0_OUT_G: R4.2, R5.2, R6.2, R7.1, TP3.1, U2.7
/C0_OUT_GO: J2.1, J3.1 (In), R10.2, U4.1
/C0_PWM_OFF: JP8.2 (B), R1.1
/C0_S_GAIN: JP5.1 (A), U5.10 (IN2)
/C0_V_OFF: R8.1, TP1.1, U1.1, U1.2 (-)
/C1_FB: R12.2, R13.2, U3.6 (-), U5.4 (S3), U5.16 (S1)
/C1_IN: JP2.1 (A), JP3.1 (A), U3.3 (+)
/C1_OUT_G: R14.2, R15.1, R16.1, R17.1, TP4.1, U3.7
/C1_OUT_GO: J2.2, J4.1 (In), R20.2, U4.7
/C1_PWM_OFF: JP6.1 (A), R11.1
/C1_S_GAIN: JP4.1 (A), U5.15 (IN1)
/C1_V_OFF: R18.1, TP2.1, U1.6 (-), U1.7
/D+: J1.3 (D+), R21.2, R23.1
/D-: J1.2 (D-), R22.2
/USB_D+: J7.12 (PA12), R21.1
/USB_D-: J7.14 (PA11), R22.1
GND: C1.2, C2.2, C3.2, C4.2, C7.2, C8.1, C9.1, C10.1, C11.2, C12.1, C13.2, C14.1, C15.2, C16.1, C17.2, C18.1, D3.1 (K), J1.4 (GND), J1.5 (Shield), J2.3, J2.4, J3.2 (Ext), J4.2 (Ext), J6.8 (GND), J6.19 (GND), J6.20 (GND), J6.22 (GND), J7.9 (GND), J7.20 (GND), L2.2, R29.1, U2.5 (+), U3.5 (+), U4.3 (+), U4.5 (+), U5.13 (GND), U6.10 (GND), U6.12 (PGND), U6.13 (GND)
unnamed: C5.1, R27.2
unnamed: C6.1, R28.2
unnamed: D1.2 (A), L1.2, U6.2 (Lx1)
unnamed: D2.1 (K), L2.1, U6.3 (Lx2)
unnamed: J6.32 (PA4), JP7.1 (A)
unnamed: J6.38 (PC0), JP8.1 (A)
unnamed: J7.11 (PA5), JP3.2 (B)
unnamed: J7.13 (PA6), JP4.2 (B)
unnamed: J7.15 (PA7), JP5.2 (B)
unnamed: J7.17 (PB6), JP6.2 (B)
unnamed: JP1.2 (B), R3.1, U2.1, U2.2 (-)
unnamed: JP2.2 (B), R13.1, U3.1, U3.2 (-)
unnamed: C1.1, R1.2, U1.3 (+)
unnamed: C2.1, R11.2, U1.5 (+)
unnamed: R6.1, R7.2, R8.2, R9.1, R10.1, U4.2 (-)
unnamed: R16.2, R17.2, R18.2, R19.1, R20.1, U4.6 (-)
unnamed: R14.1, U5.1 (D1)
unnamed: R15.2, U5.3 (D3)
unnamed: R4.1, U5.8 (D2)
unnamed: R5.1, U5.6 (D4)
unnamed: C5.2, R24.2, R29.2, U6.9 (Vfb1)
unnamed: C6.2, R25.2, R26.1, U6.6 (Vfb2)
unnamed: C4.1, R26.2, U6.7 (Vref)

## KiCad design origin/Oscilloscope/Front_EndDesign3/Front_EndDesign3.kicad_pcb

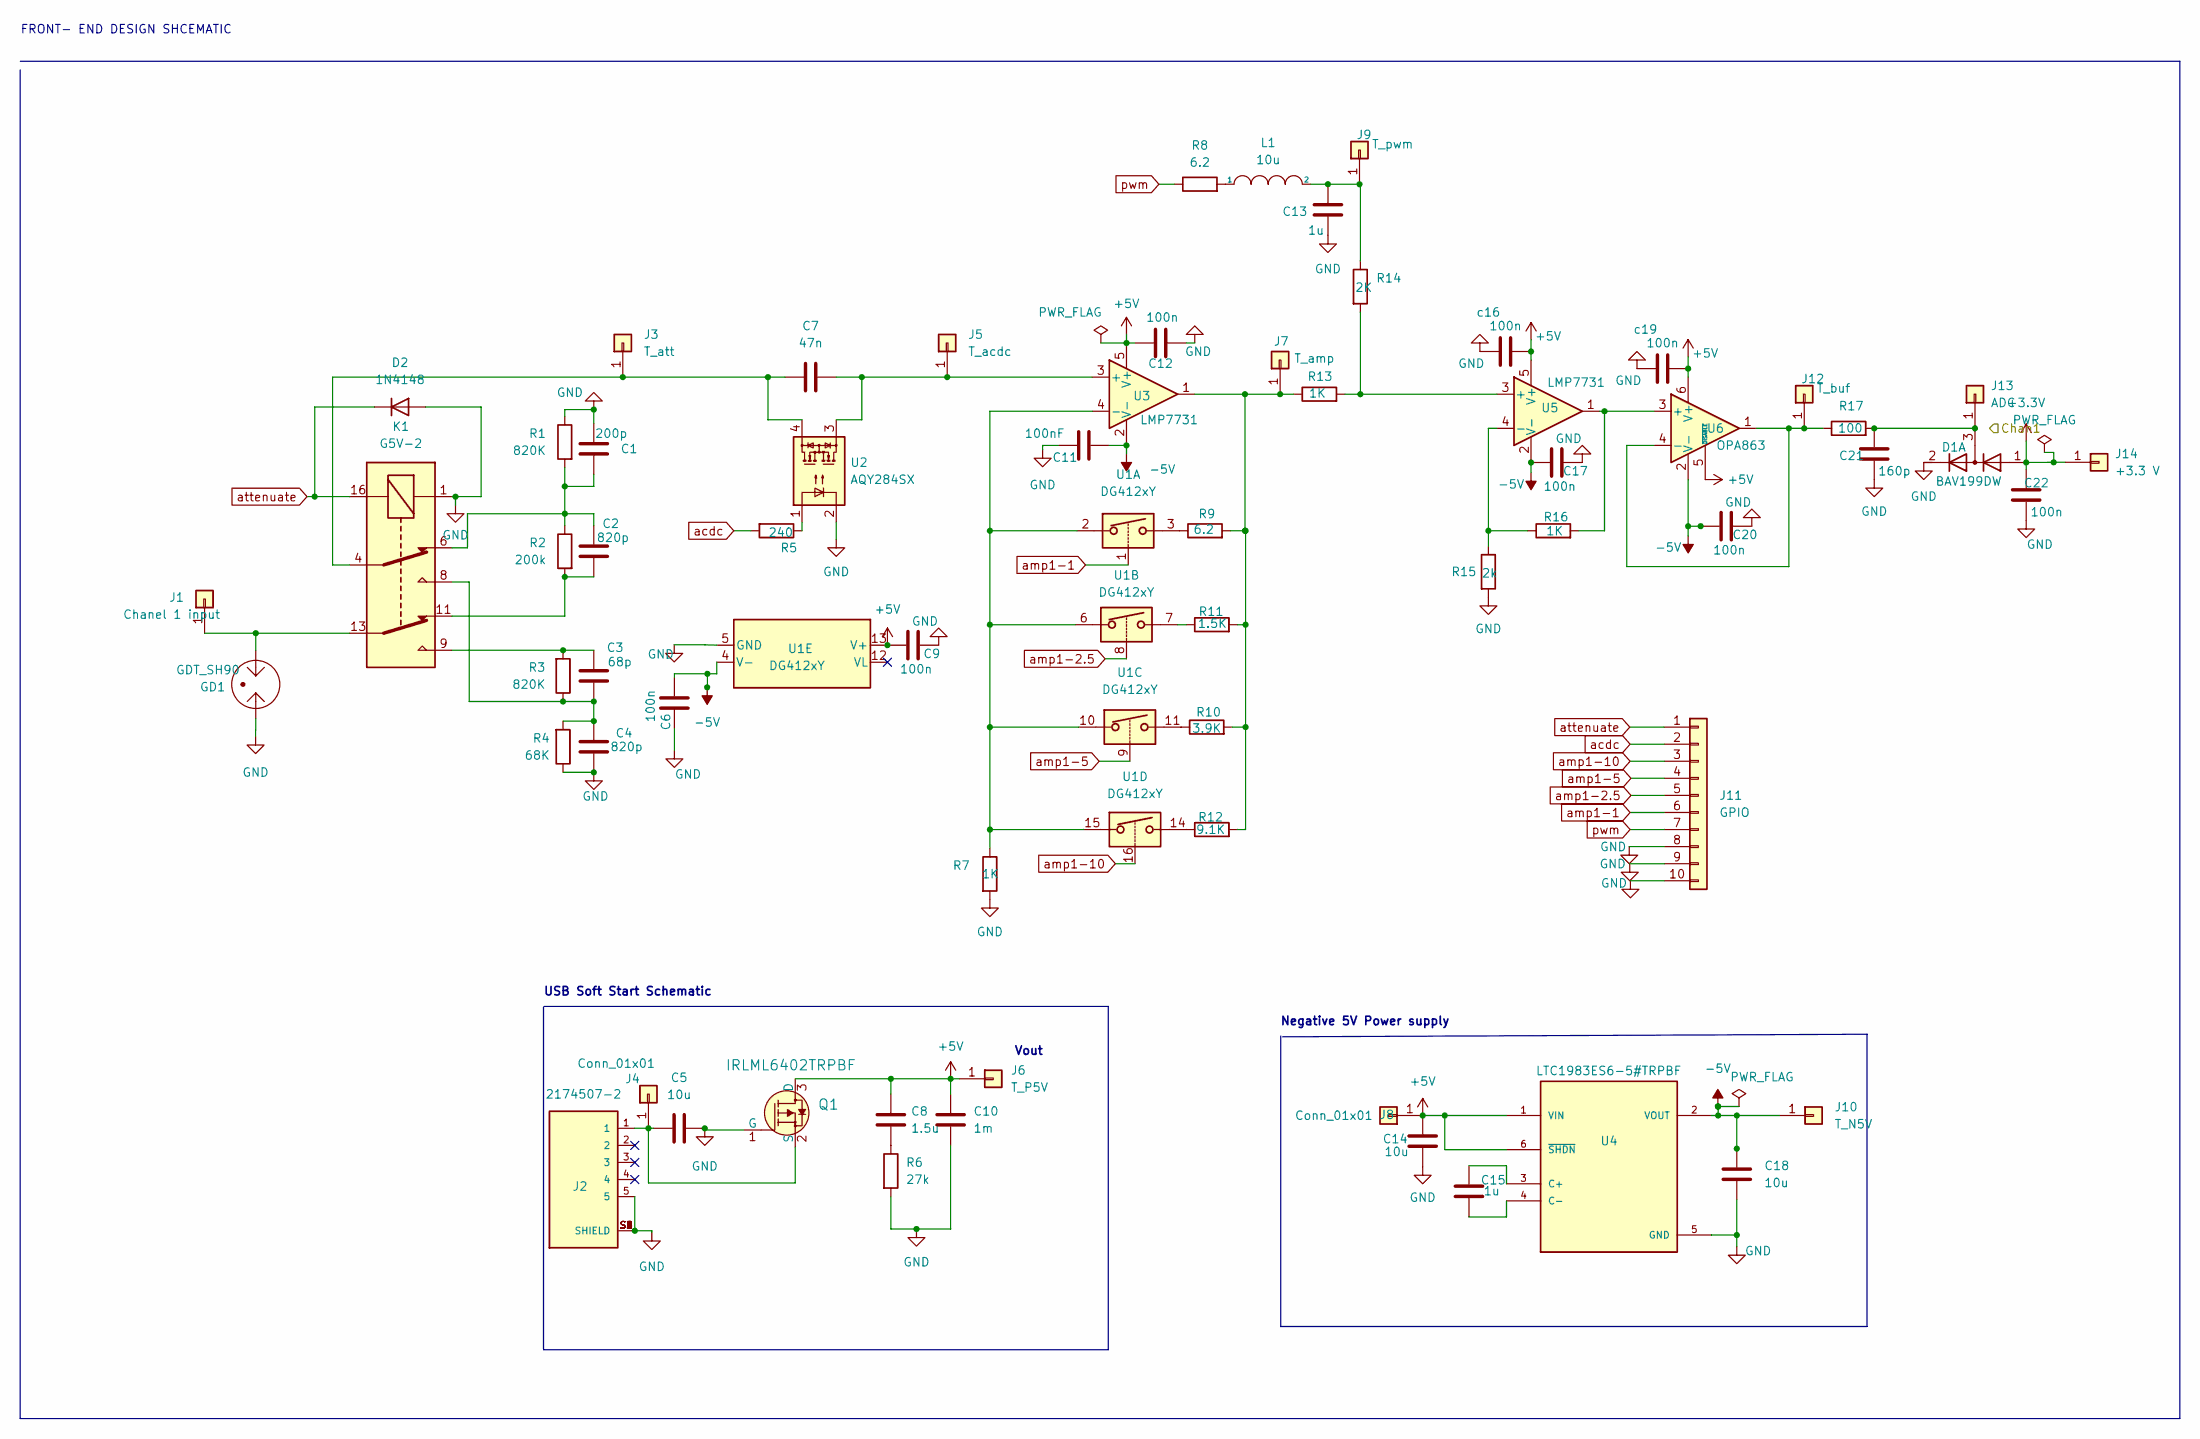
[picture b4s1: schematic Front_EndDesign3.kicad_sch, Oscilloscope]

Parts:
C1: 200p; C_0603_1608Metric_Pad1.08x0.95mm_HandSolder
C2, C4: 820p; C_0603_1608Metric_Pad1.08x0.95mm_HandSolder
C3: 68p; C_0603_1608Metric_Pad1.08x0.95mm_HandSolder
C5, C14, C18: 10u; C_0603_1608Metric_Pad1.08x0.95mm_HandSolder
C6, C9, C12, C17, C20, C22: 100n; C_0603_1608Metric_Pad1.08x0.95mm_HandSolder
C7: 47n; C_0603_1608Metric_Pad1.08x0.95mm_HandSolder
C8: 1.5u; C_0603_1608Metric_Pad1.08x0.95mm_HandSolder
C10: 1m; C_0603_1608Metric_Pad1.08x0.95mm_HandSolder
C11: 100nF; C_0603_1608Metric_Pad1.08x0.95mm_HandSolder
C13, C15: 1u; C_0603_1608Metric_Pad1.08x0.95mm_HandSolder
C21: 160p; C_0603_1608Metric_Pad1.08x0.95mm_HandSolder
D1: BAV199DW; SOT-23
D2: 1N4148; D_DO-35_SOD27_P7.62mm_Horizontal
GD1: GDT_SH90; SH90_1
J1: Chanel 1 input; PinHeader_1x01_P2.54mm_Vertical
J2: 2174507-2; J_SMD_2174507-2-5_7.8_5_2.71
J3: T_att; PinHeader_1x01_P2.54mm_Vertical
J4, J8: Conn_01x01; PinHeader_1x01_P2.54mm_Vertical
J5: T_acdc; PinHeader_1x01_P2.54mm_Vertical
J6: T_P5V; PinHeader_1x01_P2.54mm_Vertical
J7: T_amp; PinHeader_1x01_P2.54mm_Vertical
J9: T_pwm; PinHeader_1x01_P2.54mm_Vertical
J10: T_N5V; PinHeader_1x01_P2.54mm_Vertical
J11: GPIO; PinHeader_1x10_P2.54mm_Vertical
J12: T_buf; PinHeader_1x01_P2.54mm_Vertical
J13: ADC; PinHeader_1x01_P2.54mm_Vertical
J14: +3.3 V; PinHeader_1x01_P2.54mm_Vertical
K1: G5V-2; Relay_DPDT_Omron_G5V-2
L1: 10u; L_0603_1608Metric_Pad1.05x0.95mm_HandSolder
Q1: IRLML6402TRPBF; SOT-23-3; MPN IRLML6402TRPBF; Digi-Key_PN IRLML6402PBFCT-ND
R1, R3: 820K; R_0603_1608Metric_Pad0.98x0.95mm_HandSolder
R2: 200k; R_0603_1608Metric_Pad0.98x0.95mm_HandSolder
R4: 68K; R_0603_1608Metric_Pad0.98x0.95mm_HandSolder
R5: 240; R_0603_1608Metric_Pad0.98x0.95mm_HandSolder
R6: 27k; R_0603_1608Metric_Pad0.98x0.95mm_HandSolder
R7, R13, R16: 1K; R_0603_1608Metric_Pad0.98x0.95mm_HandSolder
R8, R9: 6.2; R_0603_1608Metric_Pad0.98x0.95mm_HandSolder
R10: 3.9K; R_0603_1608Metric_Pad0.98x0.95mm_HandSolder
R11: 1.5K; R_0603_1608Metric_Pad0.98x0.95mm_HandSolder
R12: 9.1K; R_0603_1608Metric_Pad0.98x0.95mm_HandSolder
R14: 2K; R_0603_1608Metric_Pad0.98x0.95mm_HandSolder
R15: 2k; R_0603_1608Metric_Pad0.98x0.95mm_HandSolder
R17: 100; R_0603_1608Metric_Pad0.98x0.95mm_HandSolder
U1: DG412xY; SOIC-16_3.9x9.9mm_P1.27mm
U2: AQY284SX; SOP-4_3.8x4.1mm_P2.54mm
U3, U5: LMP7731; SOT-23-5_HandSoldering
U4: LTC1983ES6-5#TRPBF; SOT-23-6_Handsoldering; PARTREV C
U6: OPA863; SOT-23-6_Handsoldering
c16, c19: 100n; C_0603_1608Metric_Pad1.08x0.95mm_HandSolder

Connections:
+3.3V: C22.1, D1.1 (A1), J14.1
+5V: C8.2, C9.1, C10.1, C12.1, C14.1, J6.1, J8.1, Q1.3 (D), U1.13 (V+), U3.5 (V+), U4.1 (VIN), U4.6 (~SHDN), U5.5 (V+), U6.5 (~DISABLE), U6.6 (V+), c16.2, c19.2
-5V: C6.1, C11.2, C17.1, C18.1, C20.1, J10.1, U1.4 (V-), U3.2 (V-), U4.2 (VOUT), U5.2 (V-), U6.2 (V-)
GND: C1.1, C4.2, C5.2, C6.2, C9.2, C10.2, C11.1, C12.2, C13.2, C14.2, C17.2, C18.2, C20.2, C21.2, C22.2, D1.2 (K2), D2.2 (A), GD1.2, J2.5, J2.S1 (SHIELD), J2.S2 (SHIELD), J2.S3 (SHIELD), J2.S4 (SHIELD), J2.S5 (SHIELD), J2.S6 (SHIELD), J11.8, J11.9, J11.10, K1.1, Q1.1 (G), R1.1, R4.1, R6.2, R7.2, R15.2, U1.5 (GND), U2.2, U4.5 (GND), c16.1, c19.1
unnamed: C1.2, C2.1, K1.6, R1.2, R2.1
unnamed: C2.2, K1.11, R2.2
unnamed: C3.1, K1.9, R3.2
unnamed: C3.2, C4.1, K1.8, R3.1, R4.2
unnamed: C5.1, J2.1, J4.1, Q1.2 (S)
unnamed: C7.1, J3.1, K1.4, U2.4
unnamed: C7.2, J5.1, U2.3, U3.3 (+)
unnamed: C8.1, R6.1
unnamed: C13.1, J9.1, L1.2, R14.1
unnamed: C15.1, U4.3 (C+)
unnamed: C15.2, U4.4 (C-)
unnamed: C21.1, D1.3 (K3A4), J13.1, R17.2
unnamed: GD1.1, J1.1, K1.13
unnamed: J7.1, R9.2, R10.2, R11.2, R12.2, R13.1, U3.1
unnamed: J12.1, R17.1, U6.1, U6.4 (-)
unnamed: L1.1, R8.2
unnamed: R5.1, U2.1
unnamed: R7.1, U1.2, U1.6, U1.10, U1.15, U3.4 (-)
unnamed: R9.1, U1.3
unnamed: R10.1, U1.11
unnamed: R11.1, U1.7
unnamed: R12.1, U1.14
unnamed: R13.2, R14.2, U5.3 (+)
unnamed: R15.1, R16.1, U5.4 (-)
unnamed: R16.2, U5.1, U6.3 (+)
acdc: J11.2, R5.2
amp1-1: J11.6, U1.1
amp1-2.5: J11.5, U1.8
amp1-5: J11.4, U1.9
amp1-10: J11.3, U1.16
attenuate: D2.1 (K), J11.1, K1.16
pwm: J11.7, R8.1

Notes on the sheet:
Vout
USB Soft Start Schematic
Negative 5V Power supply
FRONT- END DESIGN SHCEMATIC

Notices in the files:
MCU/Core/Src/stm32h5xx_hal_msp.c:
Copyright (c) 2024 STMicroelectronics.
All rights reserved.
This software is licensed under terms that can be found in the LICENSE file
origin/Oscilloscope/STM32_IDE_Code/main.c:
Copyright (c) 2022 STMicroelectronics.
